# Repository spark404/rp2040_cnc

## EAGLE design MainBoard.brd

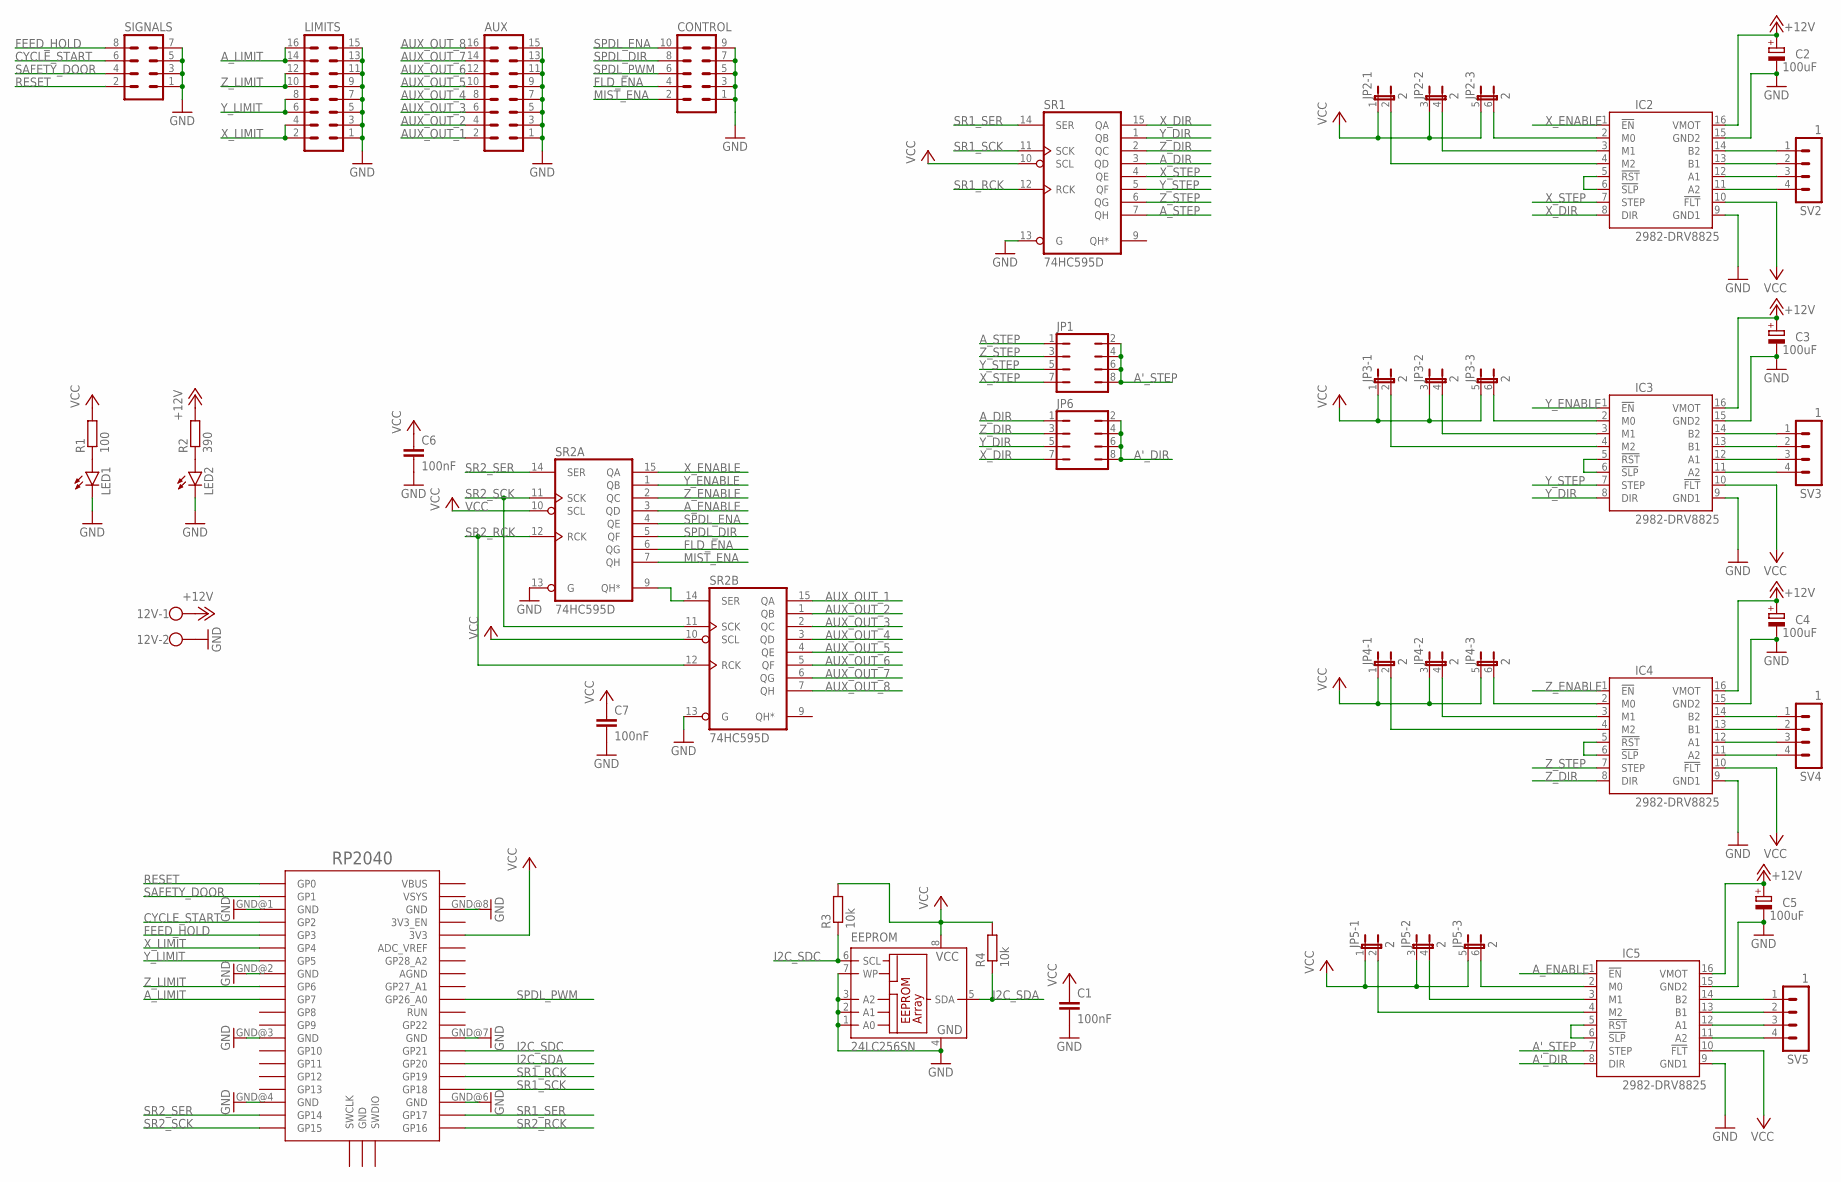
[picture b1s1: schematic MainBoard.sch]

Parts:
12V: W237-102
AUX: MA08-2
C1, C6, C7: 100nF; C0805
C2, C3, C4, C5: 100uF; E3,5-8
CONTROL: MA05-2
EEPROM: 24LC256SN; SO-08
IC2, IC3, IC4, IC5: 2982-DRV8825; DRV8825
JP1, JP6: JP4Q
JP2, JP3, JP4, JP5: 2; JP3Q
LED1, LED2: LEDCHIP-LED0805; CHIP-LED0805
LIMITS: MA08-2
R1: 100; R0805
R2: 390; R0805
R3, R4: 10k; R0805
RP2040: RPI_PICO_IG-TH; RPI_PICO_TH
SIGNALS: MA04-2
SR1, SR2A, SR2B: 74HC595D; SO16
SV2, SV3, SV4, SV5: 1; MA04-1

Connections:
+12V: 12V.1, C2.+, C3.+, C4.+, C5.+, IC2.16 (VMOT), IC3.16 (VMOT), IC4.16 (VMOT), IC5.16 (VMOT), R2.2
A'_DIR: IC5.8 (DIR), JP6.2, JP6.4, JP6.6, JP6.8
A'_STEP: IC5.7 (STEP), JP1.2, JP1.4, JP1.6, JP1.8
AUX_OUT_1: AUX.2, SR2B.15 (QA)
AUX_OUT_2: AUX.4, SR2B.1 (QB)
AUX_OUT_3: AUX.6, SR2B.2 (QC)
AUX_OUT_4: AUX.8, SR2B.3 (QD)
AUX_OUT_5: AUX.10, SR2B.4 (QE)
AUX_OUT_6: AUX.12, SR2B.5 (QF)
AUX_OUT_7: AUX.14, SR2B.6 (QG)
AUX_OUT_8: AUX.16, SR2B.7 (QH)
A_DIR: JP6.1, SR1.3 (QD)
A_ENABLE: IC5.1 (!EN), SR2A.3 (QD)
A_LIMIT: LIMITS.14, LIMITS.16, RP2040.GP7
A_STEP: JP1.1, SR1.7 (QH)
CYCLE_START: RP2040.GP2, SIGNALS.6
FEED_HOLD: RP2040.GP3, SIGNALS.8
FLD_ENA: CONTROL.4, SR2A.6 (QG)
GND: 12V.2, AUX.1, AUX.3, AUX.5, AUX.7, AUX.9, AUX.11, AUX.13, AUX.15, C1.2, C2.-, C3.-, C4.-, C5.-, C6.2, C7.2, CONTROL.1, CONTROL.3, CONTROL.5, CONTROL.7, CONTROL.9, EEPROM.1 (A0), EEPROM.2 (A1), EEPROM.3 (A2), EEPROM.4 (GND), EEPROM.7 (WP), IC2.9 (GND1), IC2.15 (GND2), IC3.9 (GND1), IC3.15 (GND2), IC4.9 (GND1), IC4.15 (GND2), IC5.9 (GND1), IC5.15 (GND2), LED1.C, LED2.C, LIMITS.1, LIMITS.3, LIMITS.5, LIMITS.7, LIMITS.9, LIMITS.11, LIMITS.13, LIMITS.15, RP2040.GND@1 (GND), RP2040.GND@2 (GND), RP2040.GND@3 (GND), RP2040.GND@4 (GND), RP2040.GND@6 (GND), RP2040.GND@7 (GND), RP2040.GND@8 (GND), SIGNALS.1, SIGNALS.3, SIGNALS.5, SIGNALS.7, SR1.8 (GND), SR1.13 (G), SR2A.8 (GND), SR2A.13 (G), SR2B.8 (GND), SR2B.13 (G)
I2C_SDA: EEPROM.5 (SDA), R4.1, RP2040.GP20
I2C_SDC: EEPROM.6 (SCL), R3.1, RP2040.GP21
M0-X: IC2.2 (M0), JP2.6 (2)
M1-X: IC2.3 (M1), JP2.4 (2)
M2-X: IC2.4 (M2), JP2.2
MIST_ENA: CONTROL.2, SR2A.7 (QH)
unnamed: SR2A.9 (QH*), SR2B.14 (SER)
unnamed: LED1.A, R1.1
unnamed: LED2.A, R2.1
unnamed: IC2.14 (B2), SV2.1
unnamed: IC2.13 (B1), SV2.2
unnamed: IC2.12 (A1), SV2.3
unnamed: IC2.11 (A2), SV2.4
unnamed: IC2.5 (!RST), IC2.6 (!SLP)
unnamed: IC3.14 (B2), SV3.1
unnamed: IC3.13 (B1), SV3.2
unnamed: IC3.12 (A1), SV3.3
unnamed: IC3.11 (A2), SV3.4
unnamed: IC3.2 (M0), JP3.6 (2)
unnamed: IC3.3 (M1), JP3.4 (2)
unnamed: IC3.4 (M2), JP3.2
unnamed: IC3.5 (!RST), IC3.6 (!SLP)
unnamed: IC4.14 (B2), SV4.1
unnamed: IC4.13 (B1), SV4.2
unnamed: IC4.12 (A1), SV4.3
unnamed: IC4.11 (A2), SV4.4
unnamed: IC4.2 (M0), JP4.6 (2)
unnamed: IC4.3 (M1), JP4.4 (2)
unnamed: IC4.4 (M2), JP4.2
unnamed: IC4.5 (!RST), IC4.6 (!SLP)
unnamed: IC5.14 (B2), SV5.1
unnamed: IC5.13 (B1), SV5.2
unnamed: IC5.12 (A1), SV5.3
unnamed: IC5.11 (A2), SV5.4
unnamed: IC5.2 (M0), JP5.6 (2)
unnamed: IC5.3 (M1), JP5.4 (2)
unnamed: IC5.4 (M2), JP5.2
unnamed: IC5.5 (!RST), IC5.6 (!SLP)
RESET: RP2040.GP0, SIGNALS.2
SAFETY_DOOR: RP2040.GP1, SIGNALS.4
SPDL_DIR: CONTROL.8, SR2A.5 (QF)
SPDL_ENA: CONTROL.10, SR2A.4 (QE)
SPDL_PWM: CONTROL.6, RP2040.GP26_A0
SR1_RCK: RP2040.GP19, SR1.12 (RCK)
SR1_SCK: RP2040.GP18, SR1.11 (SCK)
SR1_SER: RP2040.GP17, SR1.14 (SER)
SR2_RCK: RP2040.GP16, SR2A.12 (RCK), SR2B.12 (RCK)
SR2_SCK: RP2040.GP15, SR2A.11 (SCK), SR2B.11 (SCK)
SR2_SER: RP2040.GP14, SR2A.14 (SER)
VCC: C1.1, C6.1, C7.1, EEPROM.8 (VCC), IC2.10 (!FLT), IC3.10 (!FLT), IC4.10 (!FLT), IC5.10 (!FLT), JP2.1, JP2.3 (1), JP2.5 (1), JP3.1, JP3.3 (1), JP3.5 (1), JP4.1, JP4.3 (1), JP4.5 (1), JP5.1, JP5.3 (1), JP5.5 (1), R1.2, R3.2, R4.2, RP2040.3V3, SR1.10 (SCL), SR1.16 (VCC), SR2A.10 (SCL), SR2A.16 (VCC), SR2B.10 (SCL), SR2B.16 (VCC)
X_DIR: IC2.8 (DIR), JP6.7, SR1.15 (QA)
X_ENABLE: IC2.1 (!EN), SR2A.15 (QA)
X_LIMIT: LIMITS.2, LIMITS.4, RP2040.GP4
X_STEP: IC2.7 (STEP), JP1.7, SR1.4 (QE)
Y_DIR: IC3.8 (DIR), JP6.5, SR1.1 (QB)
Y_ENABLE: IC3.1 (!EN), SR2A.1 (QB)
Y_LIMIT: LIMITS.6, LIMITS.8, RP2040.GP5
Y_STEP: IC3.7 (STEP), JP1.5, SR1.5 (QF)
Z_DIR: IC4.8 (DIR), JP6.3, SR1.2 (QC)
Z_ENABLE: IC4.1 (!EN), SR2A.2 (QC)
Z_LIMIT: LIMITS.10, LIMITS.12, RP2040.GP6
Z_STEP: IC4.7 (STEP), JP1.3, SR1.6 (QG)

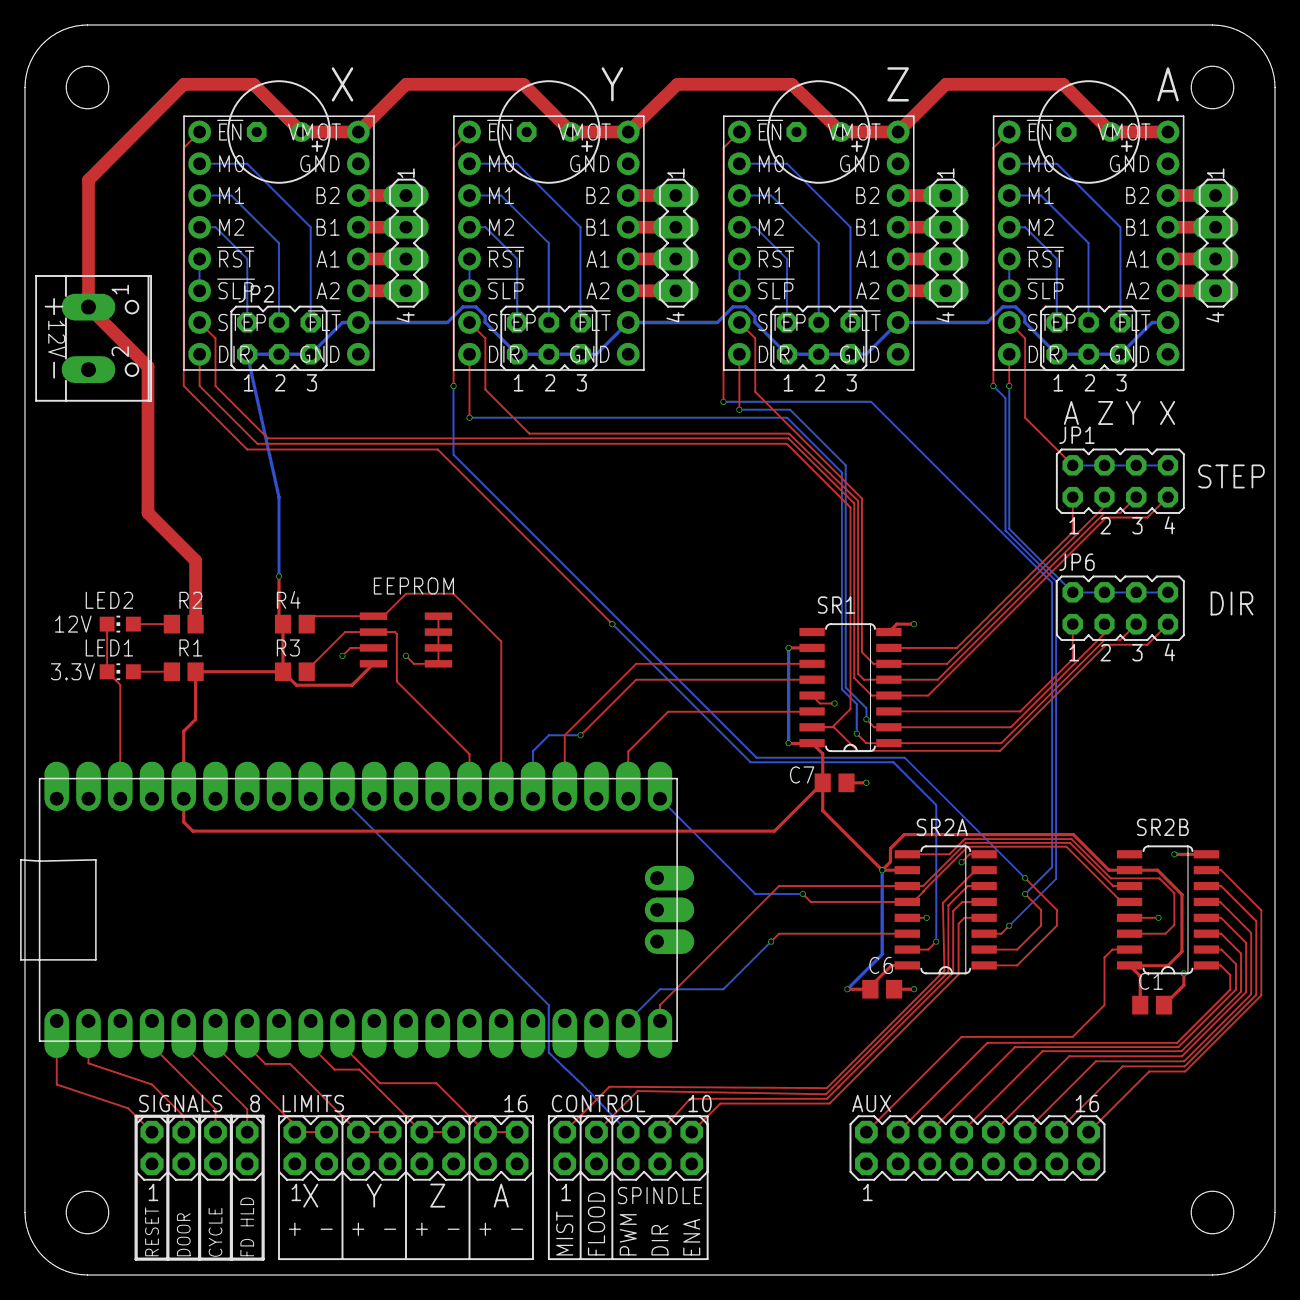
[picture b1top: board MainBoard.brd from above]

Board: 2 copper layers, 100.0 x 100.0 mm, 37 parts (0 on the bottom side), 81 nets.

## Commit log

2021-08-17 Pin 10 on the shift registers should be pulled high to enable the outputs
2022-08-03 Improved the layout a little bit and add some mounting holes
